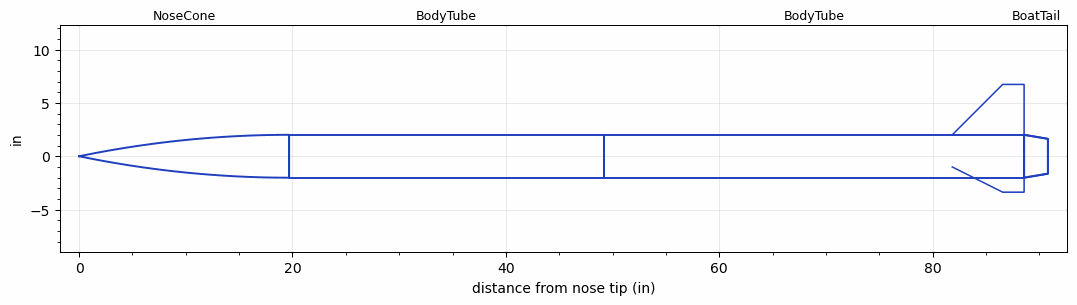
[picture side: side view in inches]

<RASAeroDocument>
 <FileVersion>2</FileVersion>
 <RocketDesign>
  <NoseCone>
   <Length>19.685</Length>
   <Diameter>4.02</Diameter>
   <Shape>Tangent Ogive</Shape>
   <Location>0</Location>
  </NoseCone>
  <BodyTube>
   <Length>29.5275</Length>
   <Diameter>4.02</Diameter>
   <Location>19.685</Location>
  </BodyTube>
  <BodyTube>
   <Length>39.37</Length>
   <Diameter>4.02</Diameter>
   <RailGuideDiameter>0.621</RailGuideDiameter>
   <RailGuideHeight>0.6845</RailGuideHeight>
   <Location>49.2125</Location>
   <BoattailLength>2.2323</BoattailLength>
   <BoattailRearDiameter>3.2677</BoattailRearDiameter>
   <Fin>
    <Count>3</Count>
    <Chord>6.7323</Chord>
    <Span>4.7244</Span>
    <SweepDistance>4.7244</SweepDistance>
    <TipChord>2.0079</TipChord>
    <Thickness>0.2461</Thickness>
    <Location>6.7323</Location>
    <AirfoilSection>Rounded</AirfoilSection>
   </Fin>
  </BodyTube>
  <BoatTail>
   <Length>2.2323</Length>
   <Diameter>4.02</Diameter>
   <RearDiameter>3.2677</RearDiameter>
   <Location>88.5825</Location>
  </BoatTail>
  <Surface>Camouflage Paint</Surface>
  <ModifiedBarrowman>False</ModifiedBarrowman>
  <Turbulence>False</Turbulence>
  <UseBooster1>False</UseBooster1>
  <UseBooster2>False</UseBooster2>
  <Comments>Changes: Eric
- Decided to use 1.2cm thick plywood for centering rings and bulkheads as opposed to 3x 0.3cm plywood stuck together for better repeatability
- Parachute weights have been changed, 600g for the main parachute and 300g for the drogue parachute. This takes into account the parachute and also the black powder system
- Payload added along with avionics. Both are 500g.
- fixed conversions from cm and mm being off (0.2 and 0.5mm thickness couplers and shoulders)
- corrected parachute sizing
- Increased mass of avionics to be more realistic
- probably make the find rounded and not airfoil, thats gonna be hard to make ngl
- maybe add a nose mass to simulate whatever you make the nose out of

Changes: EJ
-moves bulkheads, parachute, eyebolts, avionics payload postion.
-changes coupler length and shoulder length
-changes fin shape to account for changes in cal


Change: Eric
- FB bulkheads, 6mm
- General fixes to dimension

</Comments>
 </RocketDesign>
 <LaunchSite>
  <Altitude>0</Altitude>
  <Pressure>29.9214</Pressure>
  <RodAngle>0</RodAngle>
  <RodLength>118.11</RodLength>
  <Temperature>59</Temperature>
  <WindSpeed>4.4739</WindSpeed>
 </LaunchSite>
 <Recovery>
  <Altitude1>656.168</Altitude1>
  <Altitude2>984.252</Altitude2>
  <DeviceType1>Parachute</DeviceType1>
  <DeviceType2>Parachute</DeviceType2>
  <Event1>True</Event1>
  <Event2>True</Event2>
  <Size1>35.9999</Size1>
  <Size2>59.9999</Size2>
  <EventType1>Apogee</EventType1>
  <EventType2>Altitude</EventType2>
  <CD1>1.5</CD1>
  <CD2>0</CD2>
 </Recovery>
 <SimulationList>
  <Simulation>
   <SustainerEngine>8429-M2020-IM-P  (CTI)</SustainerEngine>
   <SustainerLaunchWt>29.14</SustainerLaunchWt>
   <SustainerCG>59.11</SustainerCG>
   <SustainerIgnitionDelay>0</SustainerIgnitionDelay>
   <Booster1SeparationDelay>0</Booster1SeparationDelay>
   <Booster1IgnitionDelay>0</Booster1IgnitionDelay>
   <IncludeBooster1>False</IncludeBooster1>
   <Booster2Delay>0</Booster2Delay>
   <IncludeBooster2>False</IncludeBooster2>
  </Simulation>
  <Simulation>
   <SustainerLaunchWt>15.0935</SustainerLaunchWt>
   <SustainerCG>50.3191</SustainerCG>
   <SustainerIgnitionDelay>0</SustainerIgnitionDelay>
   <Booster1SeparationDelay>0</Booster1SeparationDelay>
   <Booster1IgnitionDelay>0</Booster1IgnitionDelay>
   <IncludeBooster1>False</IncludeBooster1>
   <Booster2Delay>0</Booster2Delay>
   <IncludeBooster2>False</IncludeBooster2>
  </Simulation>
 </SimulationList>
</RASAeroDocument>
